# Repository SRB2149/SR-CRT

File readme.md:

# CRT HDMI Bridge

Live HDMI video on a vintage monochrome CRT, via a Raspberry Pi, an FPGA and a custom interface PCB.

A desktop PC outputs HDMI to a USB capture card on a Raspberry Pi Zero 2 W. The Pi downscales the feed to 296x256, dithers it to 1 bit per pixel using Atkinson dither, and streams it over SPI to an FPGA. The FPGA then drives the Amstrad GT65 CRT monitor at 50 Hz.

## Hardware

- Raspberry Pi Zero 2 W
- UVC-compliant HDMI capture card (MS2130-based works well)
- Sipeed Tang Nano 9K (or any small FPGA with LVDS output and at least 16kiB Block SRAM)
- Custom interface PCB (The files are provided if you wish to have it fabricated - or if you would rather I still have some spare which can be bought. Enquire for more info)
- Amstrad GT65 monochrome CRT monitor
- 5V power supply (Or you can use the CRT's own 5V output)

## How it works

```
PC --HDMI--> Capture Card --USB--> Pi --SPI--> FPGA --LVDS--> Interface PCB --Serial--> CRT
```

The Pi does the heavy lifting in software (capture, scale, dither). The FPGA does the time-critical CRT signal generation in hardware. SPI between them runs at 50 MHz and carries one 9472-byte framebuffer per CRT frame. The interface PCB acts as a level shifter as well as (depending on the setup) an electrical isolator. 
In theory the CRT could be directly driven using a level shifter from the FPGA, but you are on your own if you wish to attempt that.

In Windows 11 itself the monitor is set to 640x480 at 60 Hz.

The custom interface PCB once assembled

Here is the CRT showing the languages section of this repo!

## Setup

For the Raspberry Pi side, see [INSTALL.txt](RPi/INSTALL.txt). The short version:

1. Flash Raspberry Pi OS Lite (64-bit) with WiFi and SSH preconfigured
2. `scp` the contents of `RPi/` to the Pi
3. Run `./setup_pi.sh` and reboot

For the FPGA side, open the project in your toolchain of choice and flash to your board. Pin assignments are in the top-level constraints file.
You can flash the [SPI_to_CRT.fs](FPGA/SPI_to_CRT/impl/pnr/SPI_to_CRT.fs) binary file directly if you have a GW1NR-LV9C (Tang Nano 9K) FPGA. Otherwise you will need to resynthesise etc.

## Acknowledgements

The Raspberry Pi software was written by Claude (Anthropic) under my supervision. The FPGA work and the rest is mine. For enquiries, contact contact@stanleybooth.uk.

## License

This project is licensed under the MIT License — see [LICENSE](LICENSE) for details.

## Gallery

Here are some more photos of the CRT in action. These photos do not capture the real feeling of the CRT particularly well. It looks much better in real life, especially when displaying videos or things that move as the ghosting leaves a very cool effect. The dithering also provides an incredible amount of information given the limited pixels. It really has to be seen in person to truly appreciate.

Asteroids online

Firefox

A frame from the song "Hip to Be Square" by Huey Lewis and the News on youtube.

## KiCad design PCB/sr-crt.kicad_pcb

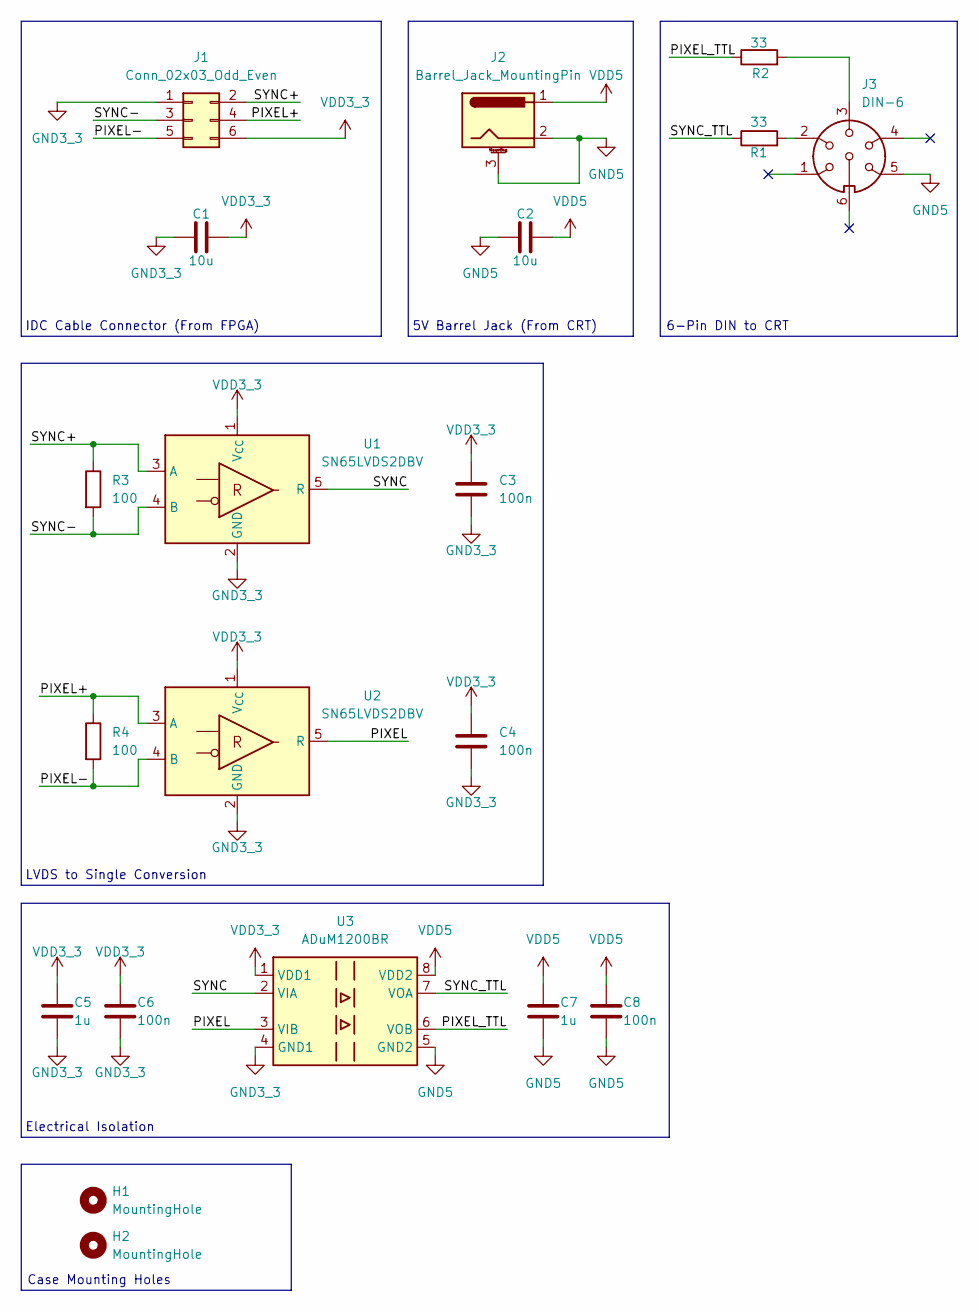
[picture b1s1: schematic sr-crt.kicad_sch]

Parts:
C1, C2: 10u; CP_Radial_D4.0mm_P2.00mm
C3, C4, C6, C8: 100n; C_0603_1608Metric
C5, C7: 1u; C_0603_1608Metric
H1, H2: MountingHole; MountingHole_2.2mm_M2_ISO7380_Pad_TopBottom
J1: Conn_02x03_Odd_Even; IDC-Header_2x03_P2.54mm_Vertical
J2: Barrel_Jack_MountingPin; BarrelJack_Horizontal
J3: DIN-6; 6_PIN_DIN
R1, R2: 33; R_0603_1608Metric
R3, R4: 100; R_0603_1608Metric
U1, U2: SN65LVDS2DBV; SOT-23-5
U3: ADuM1200BR; SOIC-8_3.9x4.9mm_P1.27mm

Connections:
/PIXEL: U2.5 (R), U3.3 (VIB)
/PIXEL+: J1.4, R4.1, U2.3 (A)
/PIXEL-: J1.5, R4.2, U2.4 (B)
/PIXEL_TTL: R2.1, U3.6 (VOB)
/SYNC: U1.5 (R), U3.2 (VIA)
/SYNC+: J1.2, R3.1, U1.3 (A)
/SYNC-: J1.3, R3.2, U1.4 (B)
/SYNC_TTL: R1.1, U3.7 (VOA)
GND3_3: C1.1, C3.2, C4.2, C5.2, C6.2, J1.1, U1.2 (GND), U2.2 (GND), U3.4 (GND1)
GND5: C2.1, C7.2, C8.2, J2.2, J2.3 (MountPin), J3.5, U3.5 (GND2)
unnamed: J3.2, R1.2
unnamed: J3.3, R2.2
VDD3_3: C1.2, C3.1, C4.1, C5.1, C6.1, J1.6, U1.1 (V_{CC}), U2.1 (V_{CC}), U3.1 (VDD1)
VDD5: C2.2, C7.1, C8.1, J2.1, U3.8 (VDD2)

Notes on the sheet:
6-Pin DIN to CRT
IDC Cable Connector (From FPGA)
5V Barrel Jack (From CRT)
LVDS to Single Conversion
Case Mounting Holes
Electrical Isolation

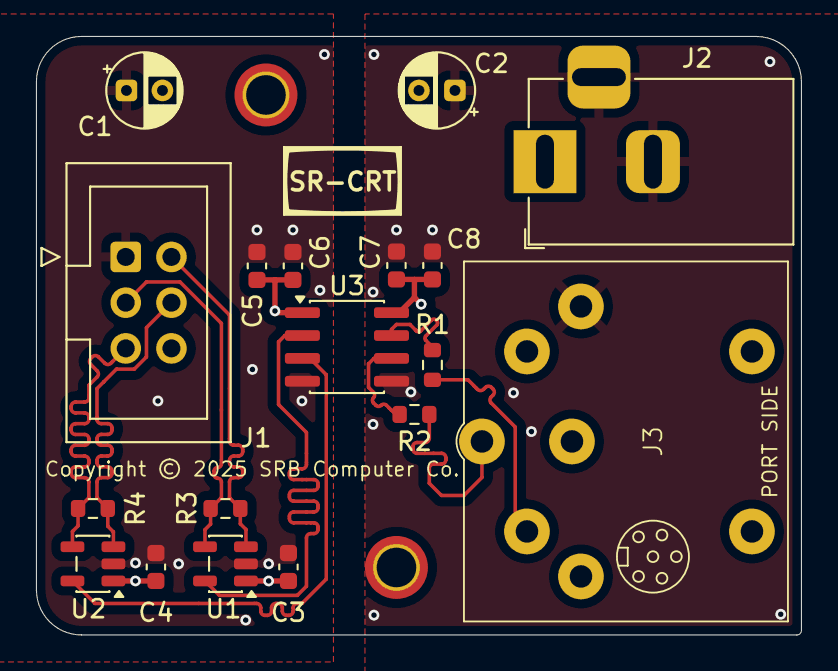
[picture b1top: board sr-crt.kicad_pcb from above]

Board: 4 copper layers, 42.5 x 33.2 mm, 20 parts (0 on the bottom side), 14 nets.

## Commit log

2025-11-08 Started Schematic
    Added nearly everything except the 6-pin DIN connector
2025-11-08 Started PCB
    Also finished the schematic (as far as I am aware). Need to make DIN 6pin footprint once the connector arrives and I can measure it
2025-11-16 Added bits to silkscreen
    As above
2025-11-23 Sent to manufacturing
    Specifically sr-crt-2.zip
2025-12-12 PCB Changes
    Note there is an error on the PCB at the moment. The middle pin on the DIN connector should be routed to the very top pin (on the footprint)
2025-12-12 Started CRT Controller
    Also added gitignore
2025-12-16 Built CRT Controller
2025-12-16 Updated PCB
    Fixed pin issues
2026-05-11 Moved PCB stuff to folder
    As above.
2026-05-11 Raspberry Pi Setup and Code
2026-05-11 Update amstrad_gt65_crt_controller.sv
    Added page switch signal to allow use of dual framebuffers.
2026-05-11 Create SPI_to_CRT.sv
    This is the top level module for the FPGA. It is designed for a tang nano 9k (GW1NR-LV9C) but could be adapted to any FPGA if needed. Feel free to contact me if you need any help.
2026-05-11 FPGA compilation things
    The FPGA should not need to be resynthesised at all as it is ready to program. Just use the SPI_to_CRT.fs file to flash program it and it should work just fine. As usual contact me if you need any he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
2026-05-11 More FPGA Compilation things
2026-05-12 Removed Gerbers
    I think these are from the original PCB which had a few errors. Removed to reduce confusion.
2026-05-12 Create LICENSE
    Added MIT license
2026-05-12 Update SPI_to_CRT.sv
    Removed 1 byte offset as issue seems to have fixed itself.
2026-05-12 Added readme and photos
    As above.
2026-05-12 Cropped photos and added PCB photo.
    As above
2026-05-13 Update readme.md
    Fixed path errors

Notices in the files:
PCB/sr-crt.kicad_pcb:
Copyright © 2025 SRB Computer Co.
